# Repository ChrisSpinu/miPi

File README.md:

# miPi
Minimal MP3 player, based on the RP2354A, with an e-ink display and that can double as a media controller.

The MP3 player part will be handled directly by the RP2354A, outputing audio through two of its GPIO pins, while the radio receiver part of it will be handled by a RDA5807m module.

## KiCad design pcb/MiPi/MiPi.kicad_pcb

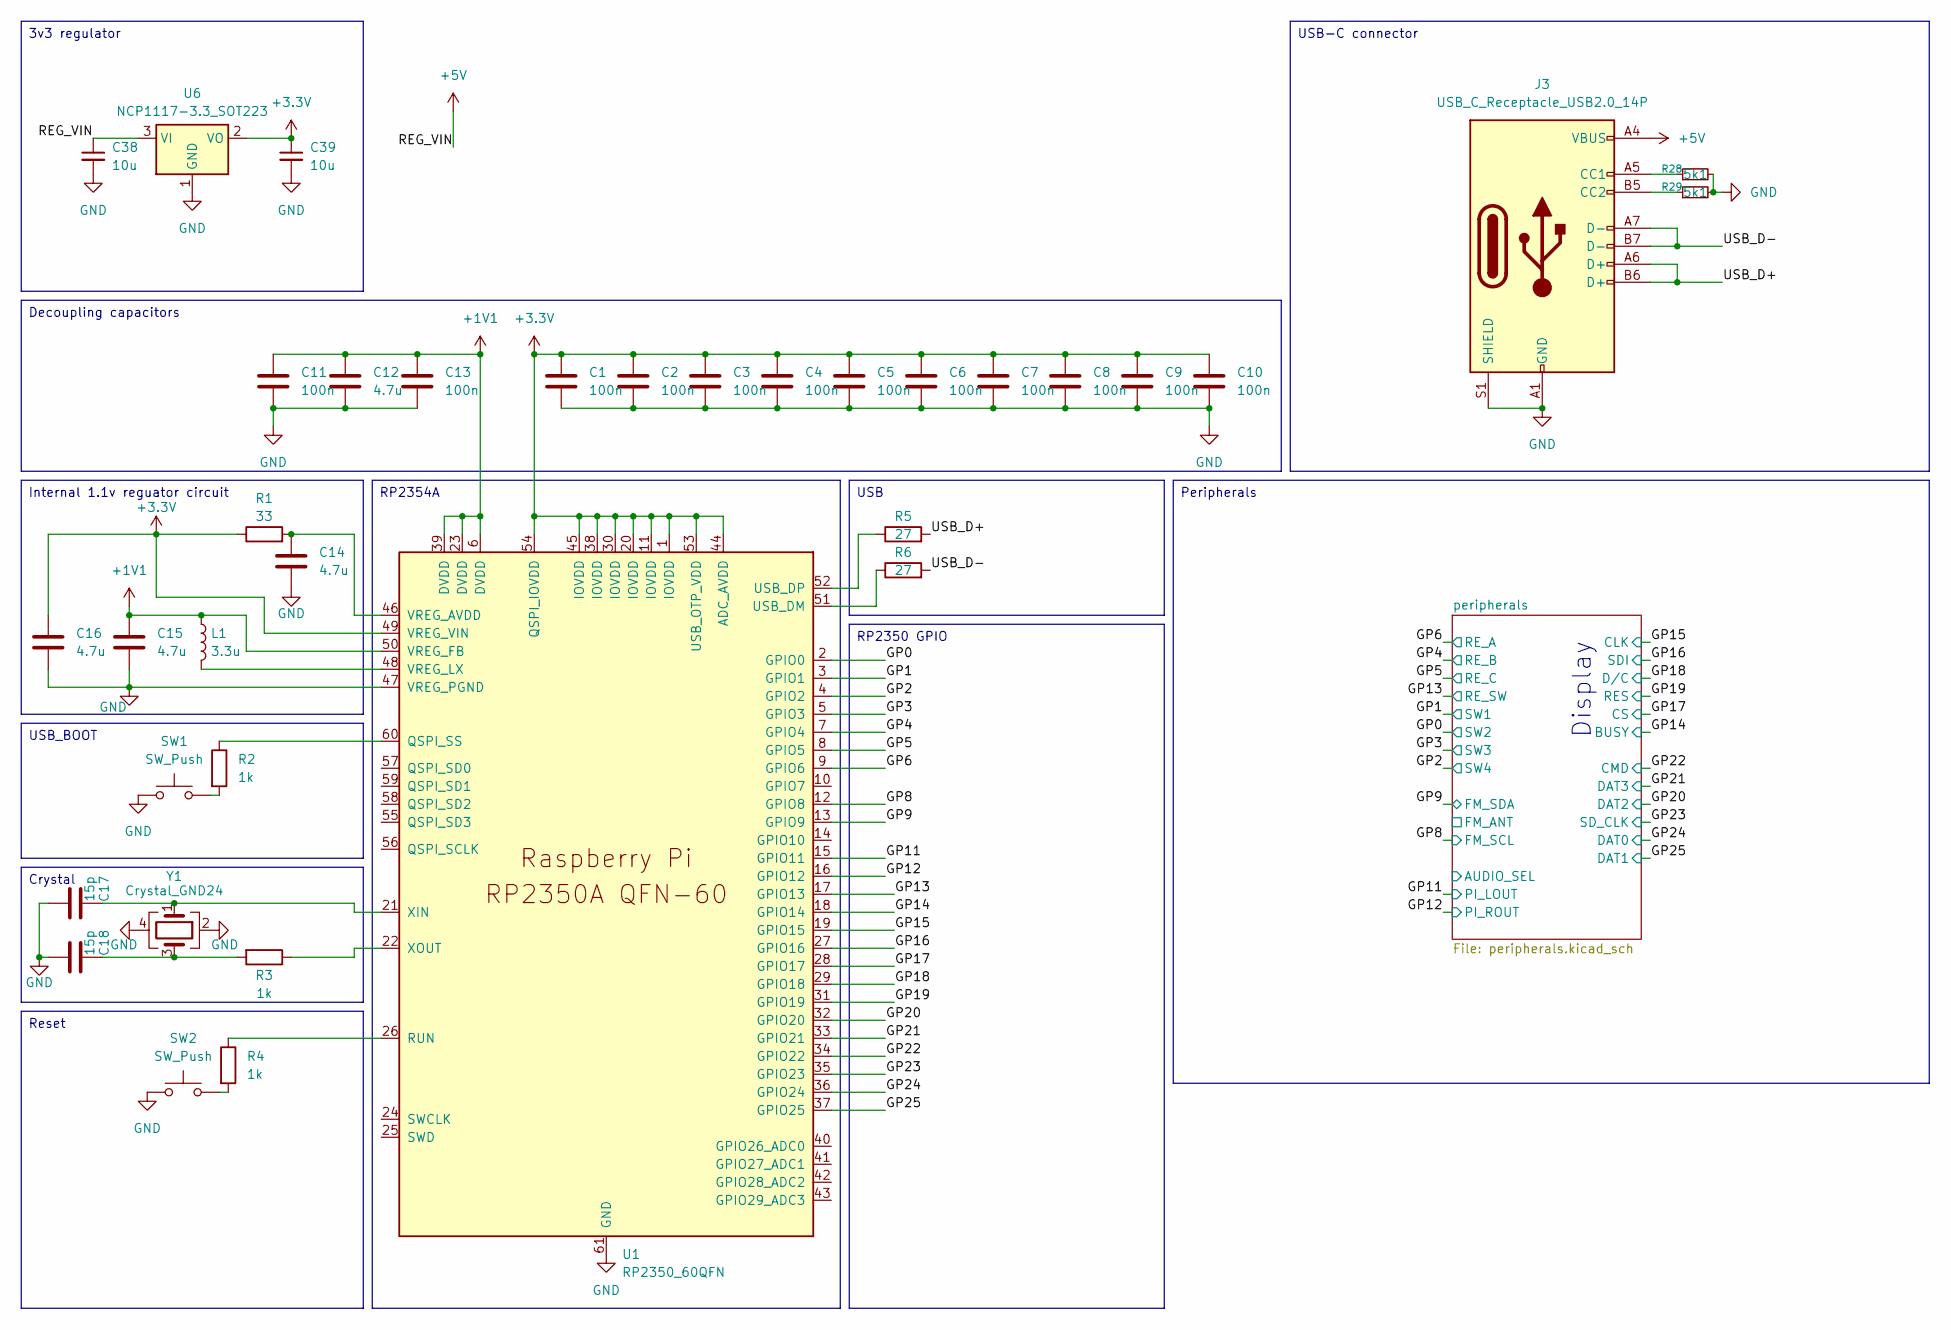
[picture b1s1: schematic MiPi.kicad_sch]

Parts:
C1, C2, C3, C4, C5, C6, C7, C8, C9, C10, C11, C13: 100n; C_0402_1005Metric; LCSC C1525
C12, C14, C15, C16: 4.7u; C_0402_1005Metric; LCSC C23733
C17, C18: 15p; C_0402_1005Metric; LCSC C86285
C38, C39: 10u; C_0402_1005Metric; LCSC C15525
J3: USB_C_Receptacle_USB2.0_14P; USB_C_Receptacle_Amphenol_124019772112A; LCSC C5430474
L1: 3.3u; L_pol_2016; LCSC C42411119
R1: 33; R_0402_1005Metric; LCSC C1091
R2, R3, R4: 1k; R_0402_1005Metric; LCSC C71623
R5, R6: 27; R_0402_1005Metric; LCSC C1091
R28, R29: 5k1; R_0402_1005Metric; LCSC C25941
SW1, SW2: SW_Push; SW_Push_1P1T_NO_CK_KMR2; LCSC C269272
U1: RP2350_60QFN; RP2350-QFN-60-1EP_7x7_P0.4mm_EP3.4x3.4mm_ThermalVias; LCSC C41378174
U6: NCP1117-3.3_SOT223; SOT-223-3_TabPin2; LCSC C26537
Y1: Crystal_GND24; Crystal_SMD_Abracon_ABM8G-4Pin_3.2x2.5mm; LCSC C20625731

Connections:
+1V1: C11.1, C12.1, C13.1, C15.1, L1.1, U1.6 (DVDD), U1.23 (DVDD), U1.39 (DVDD), U1.50 (VREG_FB)
+3.3V: C1.1, C2.1, C3.1, C4.1, C5.1, C6.1, C7.1, C8.1, C9.1, C10.1, C16.1, C39.1, R1.1, U1.1 (IOVDD), U1.11 (IOVDD), U1.20 (IOVDD), U1.30 (IOVDD), U1.38 (IOVDD), U1.44 (ADC_AVDD), U1.45 (IOVDD), U1.49 (VREG_VIN), U1.53 (USB_OTP_VDD), U1.54 (QSPI_IOVDD), U6.2 (VO); also elsewhere on the board
+5V: C38.1, J3.A4 (VBUS), J3.A9 (VBUS), J3.B4 (VBUS), J3.B9 (VBUS), U6.3 (VI)
/GP0: U1.2 (GPIO0); also elsewhere on the board
/GP1: U1.3 (GPIO1); also elsewhere on the board
/GP2: U1.4 (GPIO2); also elsewhere on the board
/GP3: U1.5 (GPIO3); also elsewhere on the board
/GP4: U1.7 (GPIO4); also elsewhere on the board
/GP5: U1.8 (GPIO5); also elsewhere on the board
/GP6: U1.9 (GPIO6); also elsewhere on the board
/GP8: U1.12 (GPIO8); also elsewhere on the board
/GP9: U1.13 (GPIO9); also elsewhere on the board
/GP11: U1.15 (GPIO11); also elsewhere on the board
/GP12: U1.16 (GPIO12); also elsewhere on the board
/GP13: U1.17 (GPIO13); also elsewhere on the board
/GP14: U1.18 (GPIO14); also elsewhere on the board
/GP15: U1.19 (GPIO15); also elsewhere on the board
/GP16: U1.27 (GPIO16); also elsewhere on the board
/GP17: U1.28 (GPIO17); also elsewhere on the board
/GP18: U1.29 (GPIO18); also elsewhere on the board
/GP19: U1.31 (GPIO19); also elsewhere on the board
/GP20: U1.32 (GPIO20); also elsewhere on the board
/GP21: U1.33 (GPIO21); also elsewhere on the board
/GP22: U1.34 (GPIO22); also elsewhere on the board
/GP23: U1.35 (GPIO23); also elsewhere on the board
/GP24: U1.36 (GPIO24); also elsewhere on the board
/GP25: U1.37 (GPIO25); also elsewhere on the board
/USB_D+: J3.A6 (D+), J3.B6 (D+), R5.2
/USB_D-: J3.A7 (D-), J3.B7 (D-), R6.2
GND: C1.2, C2.2, C3.2, C4.2, C5.2, C6.2, C7.2, C8.2, C9.2, C10.2, C11.2, C12.2, C13.2, C14.2, C15.2, C16.2, C17.2, C18.2, C38.2, C39.2, J3.A1 (GND), J3.A12 (GND), J3.B1 (GND), J3.B12 (GND), J3.S1 (SHIELD), R28.2, R29.2, SW1.1, SW2.1, U1.47 (VREG_PGND), U1.61 (GND), U6.1 (GND), Y1.2, Y1.4; also elsewhere on the board
unnamed: C18.1, R3.2, Y1.3
unnamed: J3.A5 (CC1), R28.1
unnamed: J3.B5 (CC2), R29.1
unnamed: R2.2, SW1.2
unnamed: R4.2, SW2.2
unnamed: R2.1, U1.60 (QSPI_SS)
unnamed: R4.1, U1.26 (RUN)
unnamed: R6.1, U1.51 (USB_DM)
unnamed: R5.1, U1.52 (USB_DP)
unnamed: C14.1, R1.2, U1.46 (VREG_AVDD)
unnamed: L1.2, U1.48 (VREG_LX)
unnamed: C17.1, U1.21 (XIN), Y1.1
unnamed: R3.1, U1.22 (XOUT)

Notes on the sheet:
Display
USB-C connector
USB
Decoupling capacitors
RP2350 GPIO
USB_BOOT
Crystal
RP2354A
Peripherals
3v3 regulator
Internal 1.1v reguator circuit
Reset

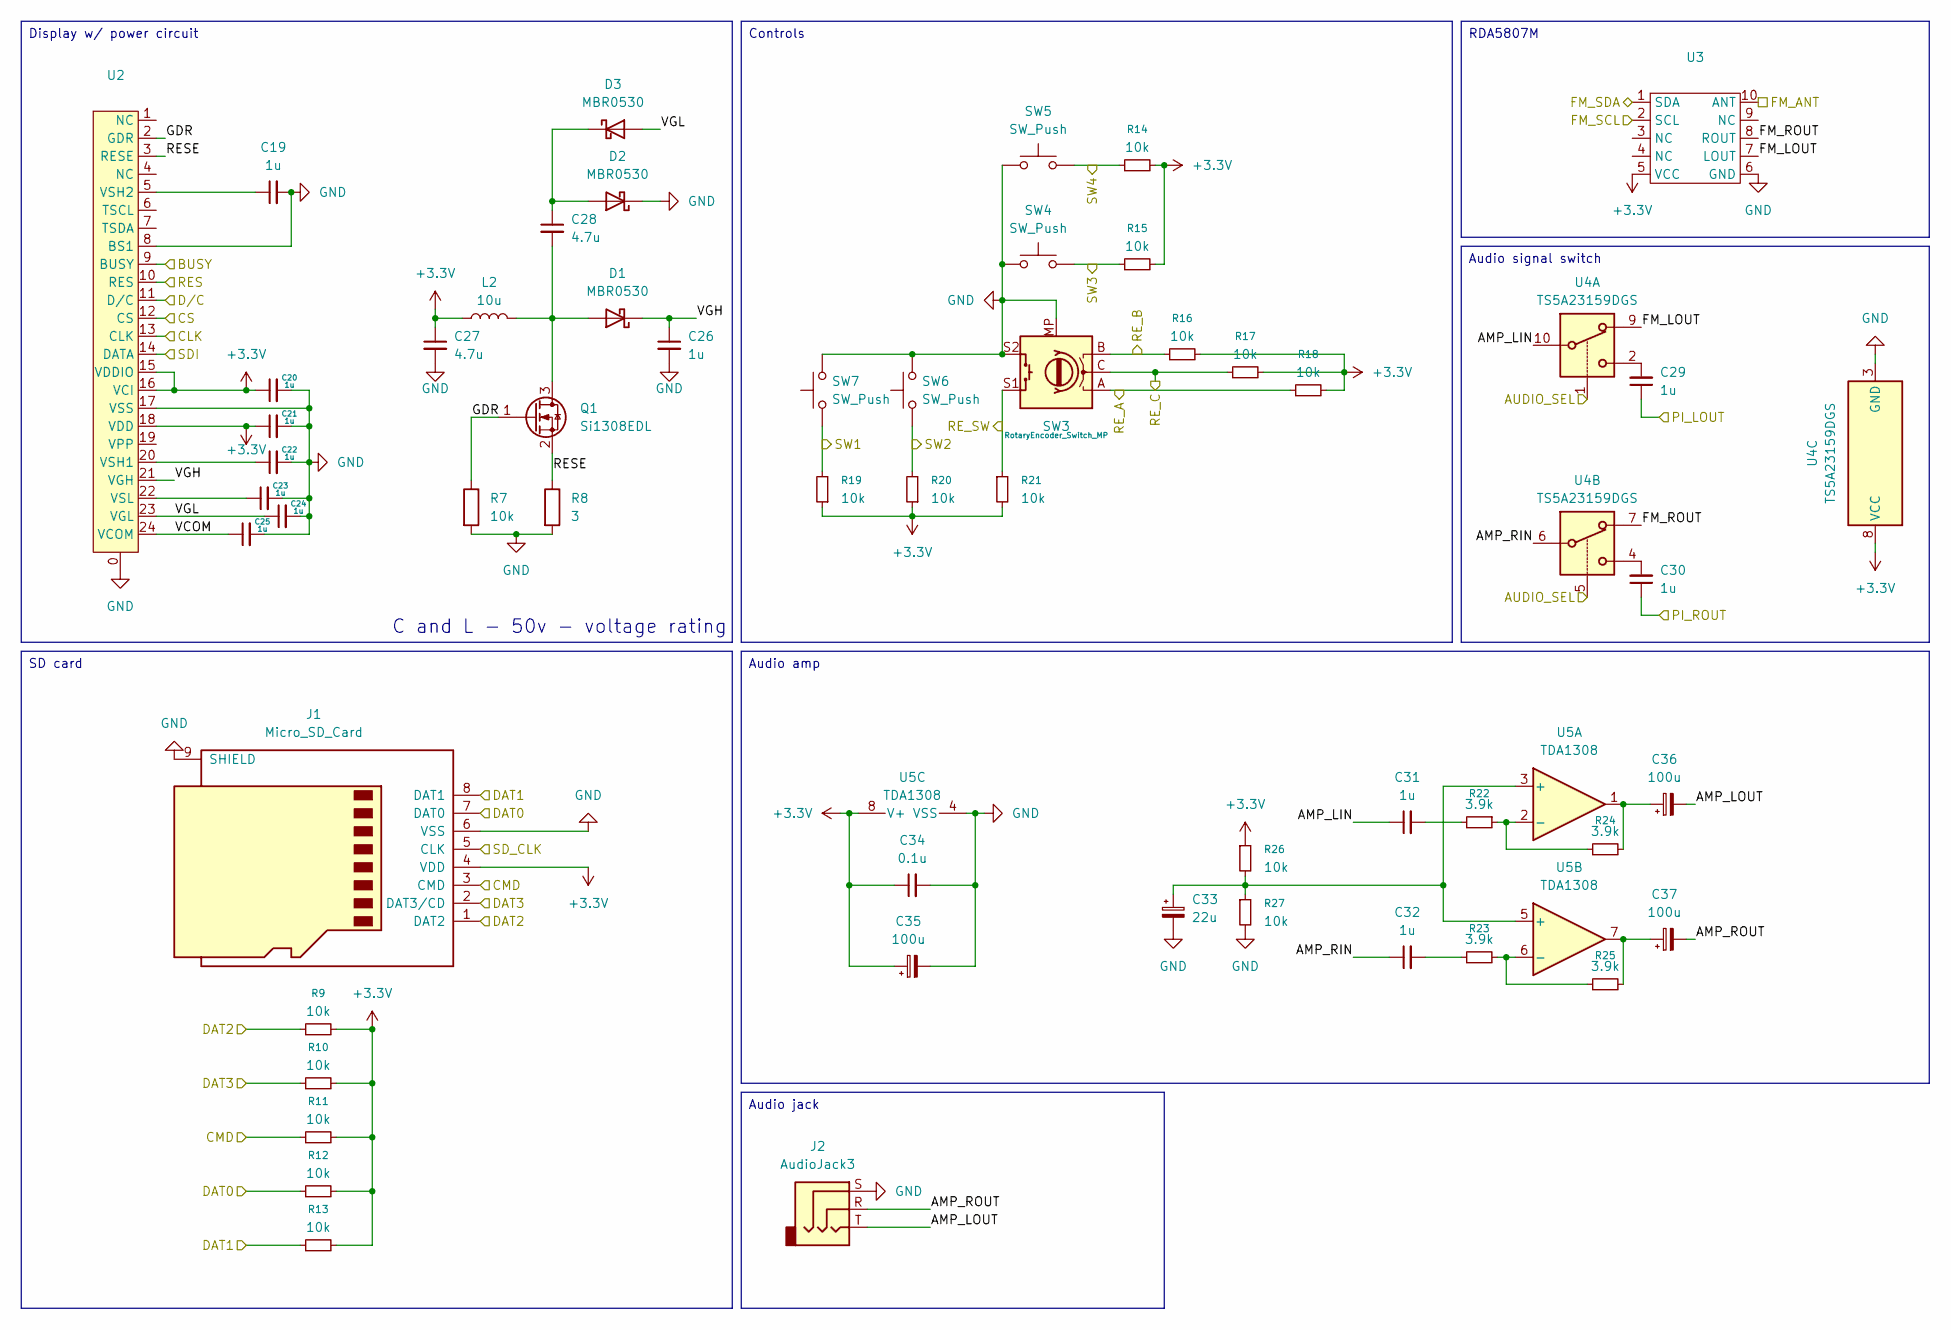
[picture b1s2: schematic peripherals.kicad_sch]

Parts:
C19, C20, C21, C22, C23, C24, C25, C26, C29, C30, C31, C32: 1u; C_0402_1005Metric; LCSC C29266
C27, C28: 4.7u; C_0402_1005Metric; LCSC C23733
C33: 22u; C_0402_1005Metric; LCSC C105226
C34: 0.1u; C_0402_1005Metric; LCSC C1525
C35, C36, C37: 100u; C_1206_3216Metric; LCSC C15008
D1, D2, D3: MBR0530; D_SOD-123; LCSC C18863
J1: Micro_SD_Card; microSD_HC_Hirose_DM3D-SF; LCSC C719027
J2: AudioJack3; Jack_3.5mm_CUI_SJ-3523-SMT_Horizontal; LCSC C4991872
L2: 10u; L_1206_3216Metric; LCSC C1051
Q1: Si1308EDL; SOT-323_SC-70; LCSC C4355112
R7, R9, R10, R11, R12, R13, R14, R15, R16, R17, R18, R19, R20, R21, R26, R27: 10k; R_0402_1005Metric; LCSC C71617
R8: 3; R_0402_1005Metric; LCSC C400520
R22, R23, R24, R25: 3.9k; R_0402_1005Metric; LCSC C278582
SW3: RotaryEncoder_Switch_MP; RotaryEncoder_Alps_EC11E-Switch_Vertical_H20mm; LCSC C202365
SW4, SW5, SW6, SW7: SW_Push; SW_Push_1P1T_NO_CK_KMR2; LCSC C269272
U2: FPC_24_TOP_CONTACTS; LCSC C22751583
U3: RDA5807M module
U4: TS5A23159DGS; VSSOP-10_3x3mm_P0.5mm; LCSC C42751
U5: TDA1308; SOIC-8_3.9x4.9mm_P1.27mm; LCSC C38340

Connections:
+3.3V: C20.1, C21.1, C27.1, C34.1, C35.1, J1.4 (VDD), L2.1, R9.2, R10.2, R11.2, R12.2, R13.2, R14.2, R15.2, R16.2, R17.2, R18.2, R19.1, R20.1, R21.2, R26.1, U2.15 (VDDIO), U2.16 (VCI), U2.18 (VDD), U3.5 (VCC), U4.8 (VCC), U5.8 (V+); also elsewhere on the board
/GP0: R20.2, SW6.1; also elsewhere on the board
/GP1: R19.2, SW7.1; also elsewhere on the board
/GP2: R14.1, SW5.2; also elsewhere on the board
/GP3: R15.1, SW4.2; also elsewhere on the board
/GP4: R16.1, SW3.B; also elsewhere on the board
/GP5: R17.1, SW3.C; also elsewhere on the board
/GP6: R18.1, SW3.A; also elsewhere on the board
/GP8: U3.2 (SCL); also elsewhere on the board
/GP9: U3.1 (SDA); also elsewhere on the board
/GP11: C29.1; also elsewhere on the board
/GP12: C30.1; also elsewhere on the board
/GP13: R21.1, SW3.S1; also elsewhere on the board
/GP14: U2.9 (BUSY); also elsewhere on the board
/GP15: U2.13 (CLK); also elsewhere on the board
/GP16: U2.14 (DATA); also elsewhere on the board
/GP17: U2.12 (CS); also elsewhere on the board
/GP18: U2.11 (D/C); also elsewhere on the board
/GP19: U2.10 (RES); also elsewhere on the board
/GP20: J1.1 (DAT2), R9.1; also elsewhere on the board
/GP21: J1.2 (DAT3/CD), R10.1; also elsewhere on the board
/GP22: J1.3 (CMD), R11.1; also elsewhere on the board
/GP23: J1.5 (CLK); also elsewhere on the board
/GP24: J1.7 (DAT0), R12.1; also elsewhere on the board
/GP25: J1.8 (DAT1), R13.1; also elsewhere on the board
/peripherals/AMP_LIN: C31.1, U4.10
/peripherals/AMP_LOUT: C36.2, J2.T
/peripherals/AMP_RIN: C32.1, U4.6
/peripherals/AMP_ROUT: C37.2, J2.R
/peripherals/AUDIO_SEL: U4.1, U4.5
/peripherals/FM_ANT: U3.10 (ANT)
/peripherals/FM_LOUT: U3.7 (LOUT), U4.9
/peripherals/FM_ROUT: U3.8 (ROUT), U4.7
/peripherals/GDR: Q1.1 (G), R7.1, U2.2 (GDR)
/peripherals/RESE: Q1.2 (S), R8.1, U2.3 (RESE)
/peripherals/VCOM: C25.1, U2.24 (VCOM)
/peripherals/VGH: C26.1, D1.1 (K), U2.21 (VGH)
/peripherals/VGL: C24.1, D3.2 (A), U2.23 (VGL)
GND: C19.2, C20.2, C21.2, C22.2, C23.2, C24.2, C25.2, C26.2, C27.2, C33.2, C34.2, C35.2, D2.1 (K), J1.6 (VSS), J1.9 (SHIELD), J2.S, R7.2, R8.2, R27.2, SW3.MP, SW3.S2, SW4.1, SW5.1, SW6.2, SW7.2, U2.0, U2.8 (BS1), U2.17 (VSS), U3.6 (GND), U4.3 (GND), U5.4 (VSS); also elsewhere on the board
unnamed: C29.2, U4.2
unnamed: C30.2, U4.4
unnamed: C31.2, R22.2
unnamed: C32.2, R23.1
unnamed: C36.1, R24.2, U5.1
unnamed: C37.1, R25.2, U5.7
unnamed: C28.2, D1.2 (A), L2.2, Q1.3 (D)
unnamed: C28.1, D2.2 (A), D3.1 (K)
unnamed: C22.1, U2.20 (VSH1)
unnamed: C19.1, U2.5 (VSH2)
unnamed: C23.1, U2.22 (VSL)
unnamed: C33.1, R26.2, R27.1, U5.3 (+), U5.5 (+)
unnamed: R22.1, R24.1, U5.2 (-)
unnamed: R23.2, R25.1, U5.6 (-)

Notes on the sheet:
C and L - 50v - voltage rating
Audio signal switch
Controls
RDA5807M
Audio amp
SD card
Audio jack
Display w/ power circuit

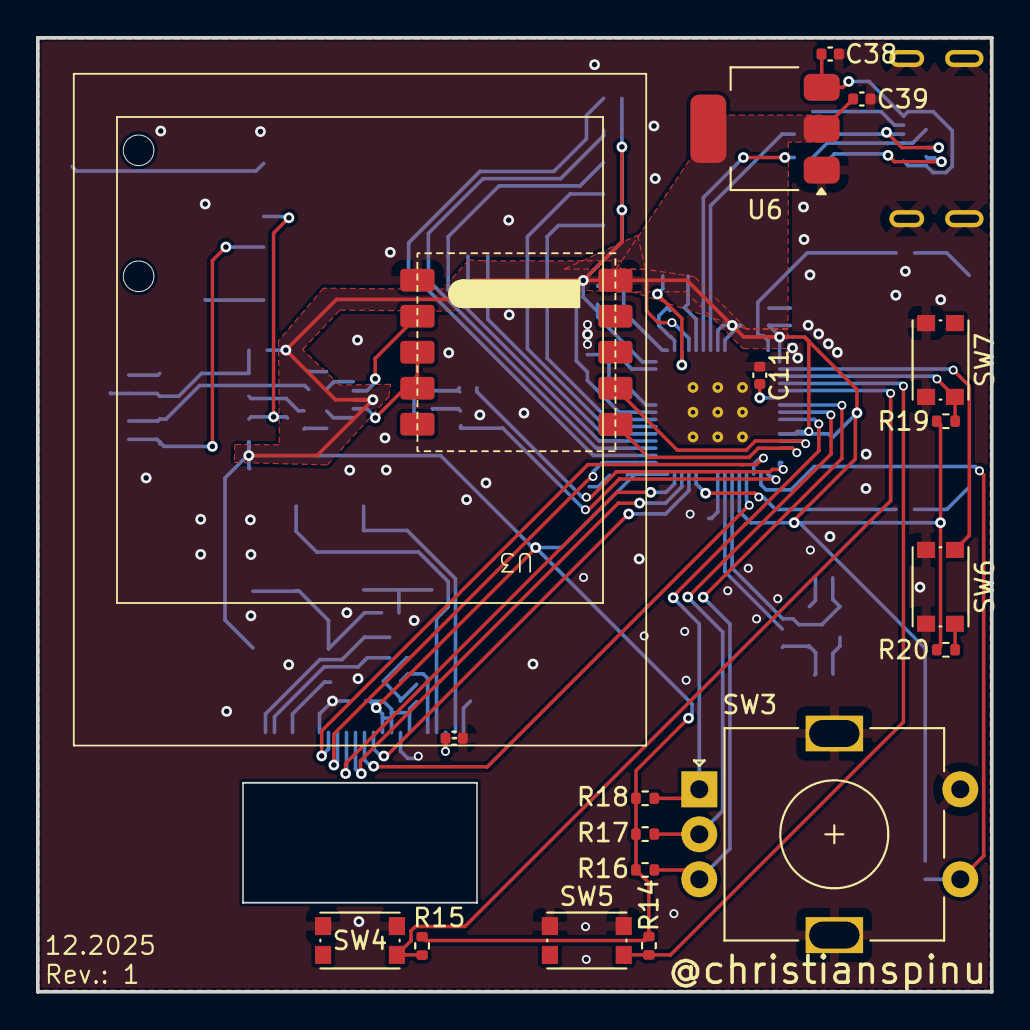
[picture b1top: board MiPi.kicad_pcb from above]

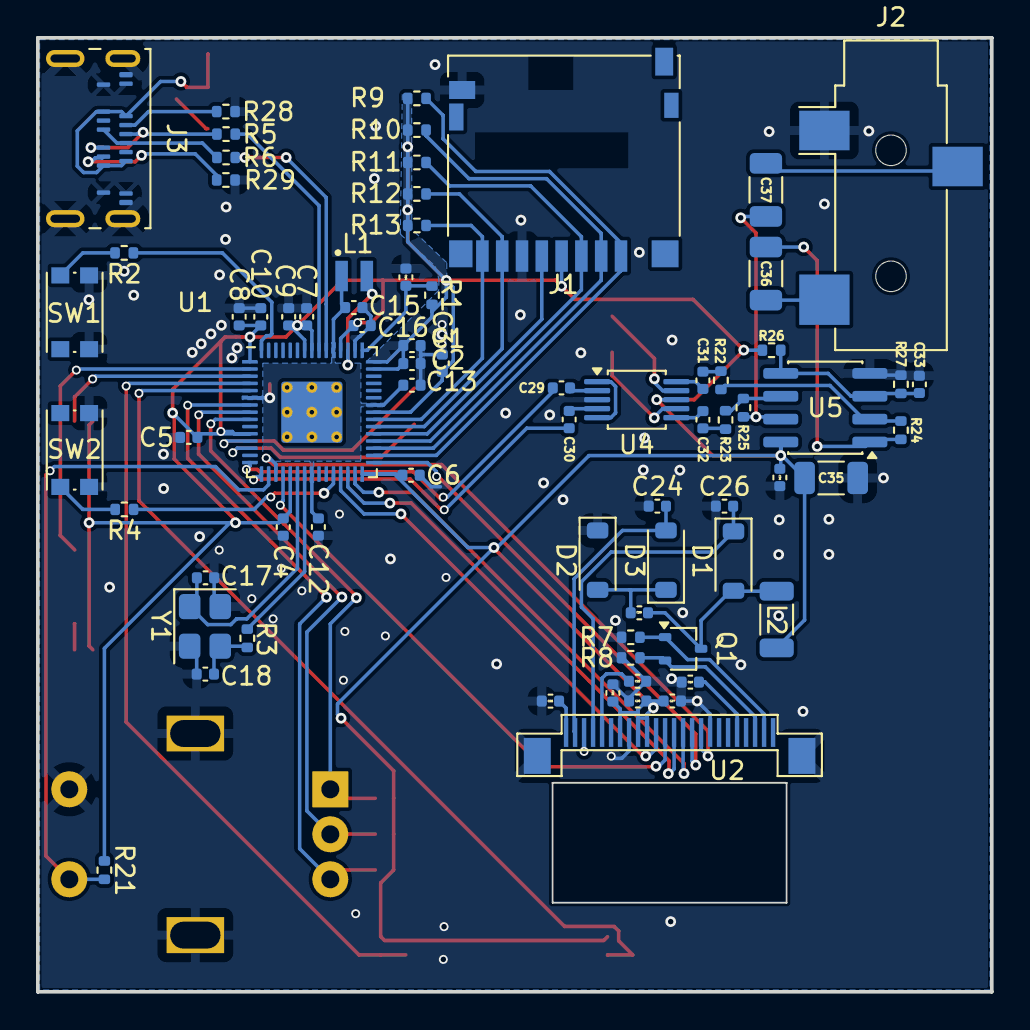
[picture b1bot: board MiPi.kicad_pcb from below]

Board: 2 copper layers, 53.0 x 53.0 mm, 91 parts (73 on the bottom side), 69 nets.

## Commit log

2025-12-17 Started the schematic design
    Almost done with the power circuitry, following the Raspberry Pi Foundation's RP2350 minimal design document.
2025-12-17 MCU chip design done
    I finished doing the RP2354A schematic design. To Do: 3v3 regulator, USB connector, check 1v1 circuitry design.
2025-12-17 Highlighted important info
2025-12-21 Update MiPi.kicad_sch
    1v1 regulator circuitry seems all right, needed to specify a capacitor's value.
2025-12-21 Display driving circuit done
2025-12-23 Did RDA5807M, controls and SD circuit schematic
2025-12-24 Peripherals sheet basically finished; Needs a check.
    Added an analog switch for selecting between the radio audio and the RP2350's audio; A headphone audio amp and an audio jack
2025-12-24 Added USB-C connector
    Remaining To Do-s: connect the peripherals to GPIO, figure out if and how to implement a rechargeable LiPo battery, 3v3 regulator, and check the all the circuit again!
2025-12-25 Started routing the PCB
    Done with the RP2350's decoupling caps, buttons and USB-C connector; Done with the display's driving circuit.
2025-12-27 Routed the analog switch and audio amp and audio jack
2025-12-28 Done the PCB layout
    Remaining ground planes and power routing
2025-12-30 Finished power routing
2025-12-30 Made a cut in the PCB
    Made a cut in the PCB where the display's FPC bends around to the back where the connector sits
2026-01-01 Made the Gerbers, BOM, and CDL for the first version of miPi
2026-01-01 Enhance README with images and detailed description
    Added images and expanded description of functionality.
